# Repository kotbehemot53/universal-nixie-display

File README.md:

Universal Nixie Display
=======================

This is the central project for the open source software and hardware for the Universal Nixie Display.
The display is something more than a desktop nixie clock - it can be whatever you want it to be by
displaying not only time but also weather data or any data you want it to display.

**At the moment it is a work in progress.**

Physical Components
-------------------

The display is modular. Each board works on its own (or with a different master), the default
configuration is:

- **Nixie board** (top): up to 6 nixie tubes (attached via pluggable socket boards with current-limiting
  trimmers, so various nixie models can be used) + up to 2 neon lamps. Driven by an ATmega328P that
  receives commands over I²C (address `0x4`).
- **VFD board** (bottom): one IV-18 8-digit 7-segment VFD tube. Driven by an ATmega328P that receives
  commands over I²C (address `0x5`).
- **Pi hat**: sits on a Raspberry Pi, sends commands to the boards above, takes power from an external
  supply and distributes it, and exposes connectors for control buttons / knobs and the power button.
- **Socket boards**: small per-tube-model boards (IN-14, Z573M) and a neon lamp board that plug into
  the nixie board.

Operating principles
--------------------

The microcontrollers provide low-level control over the displays - multiplexing, dimming, displaying
letters or digits, simple animations. The Raspberry communicates with them using I²C and sends simple
commands (what characters to display, at what brightness etc.). There are python scripts on the
Raspberry that can obtain various data (e.g. weather data from Ruuvi sensors, time from an RTC,
whatever else the user wants) and pass it to be displayed on the nixies and VFD using provided python
libraries that wrap the microcontroller commands in an easy-to-use API.

By default the nixies are meant to be used as the "main" display, whereas the VFD is a "secondary"
display, used to show currently chosen options etc. But it's up to the user to decide how they want to
use them.

Repository layout
-----------------

```
firmware/
  nixie-controller/   PlatformIO project, ATmega328P firmware for the nixie board
  vfd-controller/     PlatformIO project, ATmega328P firmware for the VFD board
software/
  raspberry/          Python scripts + systemd units for the Raspberry Pi master
hardware/
  nixie-board/        KiCad project of the nixie board
  vfd-board/          KiCad project of the VFD board
  pi-hat/             KiCad project of the Raspberry Pi hat
  sockets/            KiCad projects of the tube socket boards (in14, z573m, neon)
  lib/                Shared KiCad symbol / footprint / 3D libraries used by the boards above
scratch/
  kicad-experiments/  Throwaway KiCad experiments, not part of the product
```

See `hardware/README.md` for the board naming history, PCB variants and fabrication files.

Each firmware directory is a self-contained PlatformIO project - open it directly in PlatformIO / your
IDE. Everything in this repository is licensed under the GPLv3 (see `LICENSE`).

History
-------

This repository was assembled from several previous ones (the firmware and Raspberry code used to live
in separate repos pulled in as git submodules, the hardware lived in an older private repo). Their git
histories were rewritten into subdirectories and merged here, so `git log --follow` works on the
imported files. Old feature branches were kept under the `nixie-controller/`, `vfd-controller/` and
`raspberry/` branch prefixes, VFD firmware releases are tagged `vfd-controller/<version>`.

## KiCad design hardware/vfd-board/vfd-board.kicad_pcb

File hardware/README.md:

Hardware
========

KiCad projects for all boards of the Universal Nixie Display. Files are KiCad 6/7 format
(`kicad_sch` version 20211123 / 20230121, `kicad_pcb` version 20211014 / 20221018), open them with
KiCad 7 or newer and let it upgrade the format when you first save.

```
nixie-board/    top board: up to 6 nixies + 2 neons, ATmega328P, I2C slave 0x4
vfd-board/      bottom board: IV-18 VFD, ATmega328P, I2C slave 0x5
pi-hat/         Raspberry Pi hat: power in, I2C master, buttons / knobs, power button
sockets/
  in14/         IN-14 nixie socket board (plugs into nixie-board)
  z573m/        Z573M nixie socket board (plugs into nixie-board)
  neon/         neon lamp board (plugs into nixie-board)
lib/            shared symbol / footprint / 3D model libraries (see lib/README.md)
```

Every board directory has the same shape:

- `<board>.kicad_pro / .kicad_sch / .kicad_pcb` - the current design,
- `<board>-bom.csv` - BOM exported from the schematic (where one existed),
- `sym-lib-table` / `fp-lib-table` - project library tables, all pointing into `../lib` (or `../../lib`
  for the socket boards) via `${KIPRJMOD}`,
- `fab/` - gerber zips that were actually sent to a fab house, kept as-is for reference,
- `variants/` - alternative PCB layouts of the same schematic (autorouter pre-fills, different track
  styles, earlier revisions). They are standalone `.kicad_pro` + `.kicad_pcb` pairs, open them directly.
  They are kept for reference only, the file next to the `.kicad_sch` is the current one,
- `images/` - schematic exports and 3D renders.

Symbols and footprints are embedded in the schematic / PCB files, so the boards open and render even if
a library entry is missing. The library tables only matter when you want to update a part from its
library.

Checking library resolution
---------------------------

Library links were verified headless with KiCad 10.0.1 (`kicad-cli pcb drc` / `sch erc` with
`--severity-all`, then filter for `lib_footprint_issues` / `lib_symbol_issues`). All project libraries
resolve. The remaining "not found in library" reports come from parts that the *official* KiCad
libraries renamed or removed since the boards were drawn, not from this repository:

| Reference in the design                              | Boards                 | Status in KiCad 10 official libs                          |
|------------------------------------------------------|------------------------|-----------------------------------------------------------|
| `Button_Switch_THT:SW_TH_Tactile_Omron_B3F-10xx`     | nixie-board, vfd-board | split into `SW_TH_Tactile_Omron_B3F-100x` / `-102x` / ... |
| `Symbol:Symbol_HighVoltage_Type2_CopperTop_VerySmall`| nixie-board, vfd-board | removed, only `Symbol_HighVoltage_Triangle_*` remain      |
| `Connector:Conn_01x02_Male` / `_Female` / `Conn_01x03_Male` / `Conn_01x07_Female` | nixie-board, vfd-board, sockets | moved to `Connector_Generic`     |
| `Device:Q_NMOS_SGD`, `Device:Q_NPN_CBE`             | pi-hat-tht variant     | replaced by `Q_NMOS_GSD` / `Q_NPN_BCE` pin-order variants |

The `variants/` directories carry their own `fp-lib-table` / `sym-lib-table` (same entries, one `../`
deeper), because KiCad treats whatever directory the `.kicad_pro` sits in as the project root.

The embedded copies still work, so nothing needs to change unless a part is re-placed from the library.
"Does not match its copy in the library" warnings are expected for the same reason (embedded 2022/2023
copies vs. current library versions). `kibuzzard-*` footprints are text labels generated by the
KiBuzzard plugin and never had a library.

3D models
---------

Standard-library 3D models are referenced as `${KICAD6_3DMODEL_DIR}/<lib>.3dshapes/<name>.step`. KiCad 7+
maps the old versioned variable to the current install automatically. The references were originally
`.wrl`; KiCad 9+ ships only `.step` files and does *not* fall back from `.wrl` to `.step`, so every
generic part rendered as missing until the extensions were rewritten. Five models were dropped or renamed
upstream and still show as missing in the 3D viewer, which is cosmetic:

| Model                                                             | Board                   |
|-------------------------------------------------------------------|-------------------------|
| `Potentiometer_THT/Potentiometer_Bourns_3386F_Vertical` (9x)      | nixie-board             |
| `Button_Switch_THT/SW_TH_Tactile_Omron_B3F-10xx`                  | vfd-board               |
| `Module/Raspberry_Pi_Zero_Socketed_THT_FaceDown_MountingHoles`    | vfd-board, pi-hat       |
| `Connector_USB/USB_Micro-B_Amphenol_10103594-0001LF_Horizontal`   | pi-hat                  |
| `Connector_Wire/SolderWire-0.75sqmm_1x02_P4.8mm_D1.25mm_OD2.3mm`  | pi-hat                  |

Vendored SamacSys models live in `lib/SamacSys_Parts.3dshapes/` and are referenced via `${KIPRJMOD}`.

Naming history
--------------

The boards were renamed when the projects were moved into this repository. Old names still appear in
title blocks, net names and library nicknames (`Nixiecock1`, `nixieCockB`), which were intentionally
left alone so nothing inside the design files had to be touched apart from 3D model paths.

| Old project (piclock repo)       | Here                    | Notes                                              |
|----------------------------------|-------------------------|----------------------------------------------------|
| `kicad/nixiecock1`               | `nixie-board`           | "Board A"                                          |
| `kicad/nixiecockB`               | `vfd-board`             | "Board B"                                          |
| `kicad/pihat/pihat` `pihat_smd.kicad_sch/.kicad_pro` | `pi-hat`  | SMD version, current schematic                     |
| `kicad/pihat/pihat` `pihat_smd-rounded-blah.kicad_pcb` | `pi-hat.kicad_pcb` | current layout (rounded tracks), the one that was fabbed |
| `kicad/pihat/pihat` `pihat_smd.kicad_pcb` | `pi-hat/variants/pi-hat_unrounded` | same layout before track rounding      |
| `kicad/pihat/pihat` `pihat.*`    | `pi-hat/variants/pi-hat-tht` | older THT version, has its own schematic      |
| `kicad/IN-14Board`               | `sockets/in14`          | file names unchanged (`in14board.*`)               |
| `kicad/z573mBoard`               | `sockets/z573m`         | file names unchanged (`z573mBoard.*`)              |
| `kicad/neonBoard`                | `sockets/neon`          | file names unchanged (`neonBoard.*`)               |
| `kicad/xprmnt`                   | `../scratch/kicad-experiments` | was gitignored before                       |

Fabrication files vs. layouts (from file timestamps, verify before reusing):

- `pi-hat/fab/gerber5.zip` matches `pi-hat.kicad_pcb` (the rounded-track layout).
- `nixie-board/fab/gerber_A2`, `gerber_A3` and `vfd-board/fab/gerber_B1..B3` predate the last PCB
  edits of those boards; treat the highest number as the last one ordered.
- `sockets/in14/fab/gerbers7.zip` and `sockets/z573m/fab/gerber3.zip` match the current PCBs.

What was dropped on import
--------------------------

Regenerable or per-user files were not carried over: `*-backups/`, `.history/`, `fp-info-cache`,
`*.kicad_prl`, `*.kicad_sch-bak`, `*.xml` netlists, lock files, unzipped gerber directories that also
existed as zips, and the vendor library zips (`KiCadLibs-master.zip`, SamacSys `LIB_*.zip`) whose
relevant content is now in `lib/`.

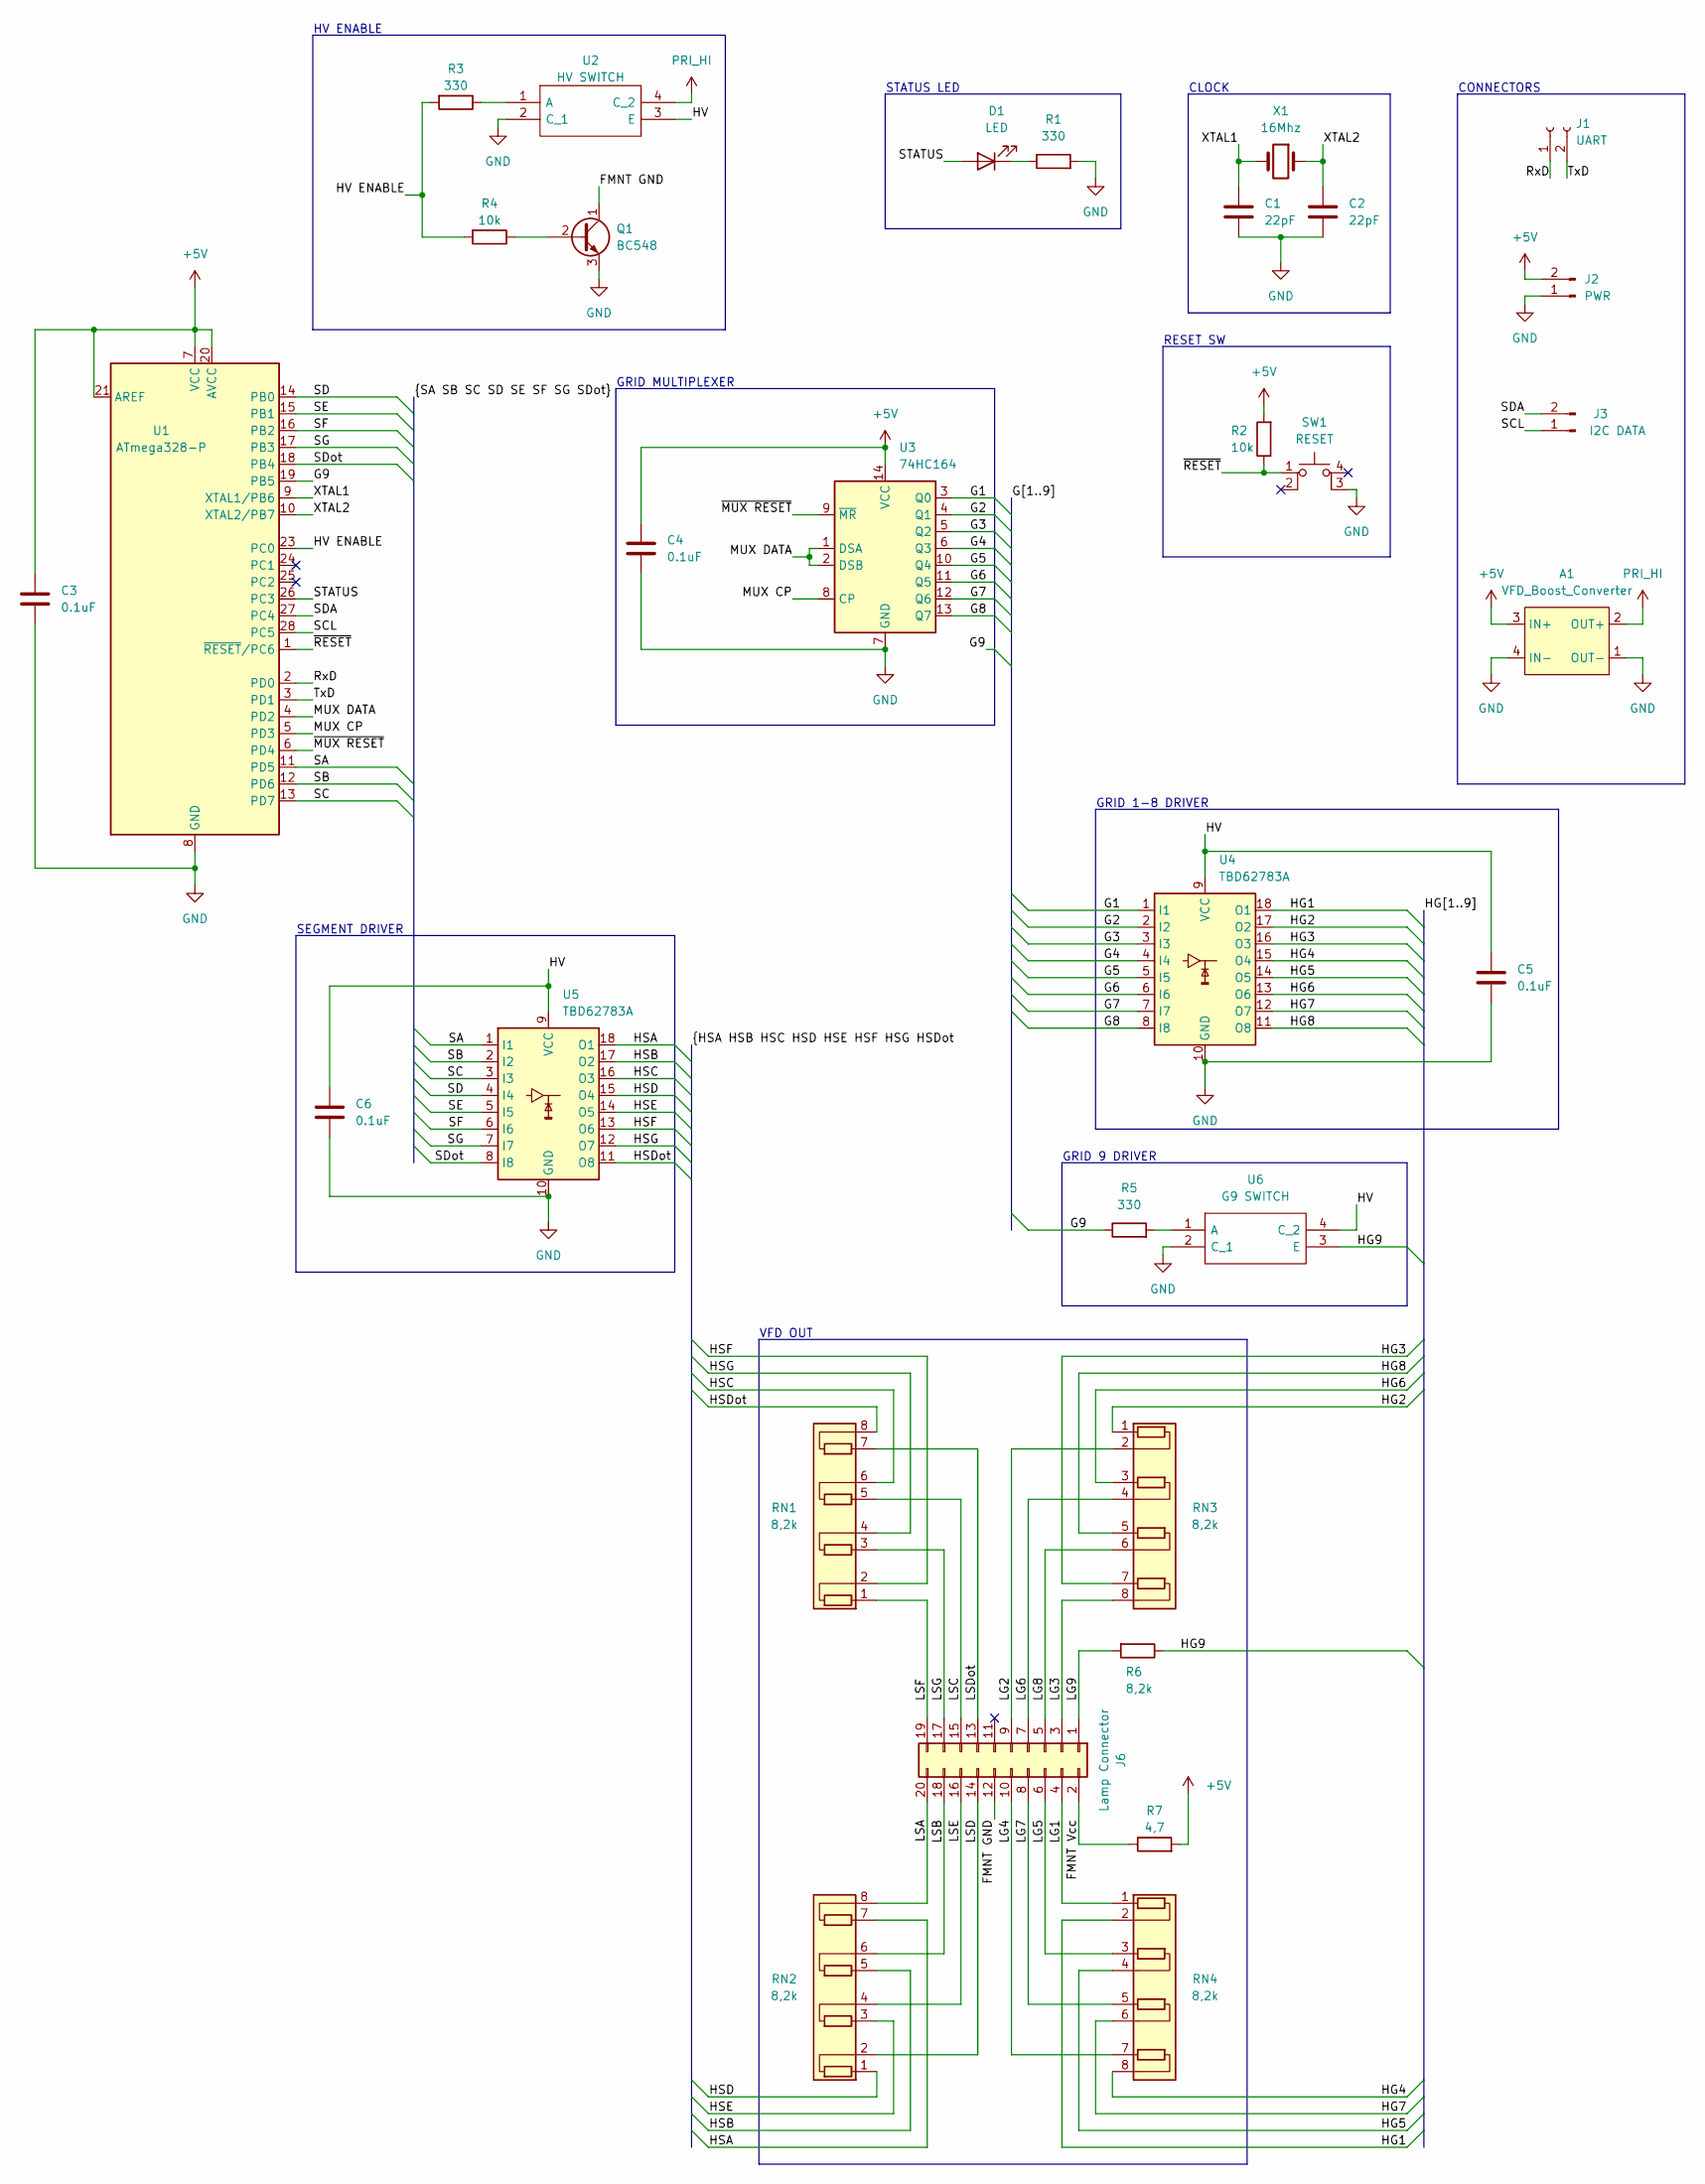
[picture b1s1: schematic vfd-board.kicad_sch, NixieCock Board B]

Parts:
A1: VFD_Boost_Converter; VFD Boost Converter
C1, C2: 22pF; C_Disc_D3.0mm_W1.6mm_P2.50mm
C3, C4, C5, C6: 0.1uF; C_Disc_D5.0mm_W2.5mm_P2.50mm
D1: LED; LED_D3.0mm
J1: UART; PinHeader_1x02_P2.54mm_Vertical
J2: PWR; JST_XH_B2B-XH-A_1x02_P2.50mm_Vertical
J3: I2C DATA; JST_XH_B2B-XH-A_1x02_P2.50mm_Vertical
J6: Lamp Connector; IDC-Header_2x10_P2.54mm_Vertical
Q1: BC548; TO-92_Inline
R1, R3, R5: 330; R_Axial_DIN0207_L6.3mm_D2.5mm_P10.16mm_Horizontal
R2, R4: 10k; R_Axial_DIN0207_L6.3mm_D2.5mm_P10.16mm_Horizontal
R6: 8,2k; R_Axial_DIN0207_L6.3mm_D2.5mm_P10.16mm_Horizontal
R7: 4,7; R_Axial_DIN0207_L6.3mm_D2.5mm_P10.16mm_Horizontal
RN1, RN2, RN3, RN4: 8,2k; R_Array_SIP8
SW1: RESET; SW_TH_Tactile_Omron_B3F-10xx
U1: ATmega328-P; DIP-28_W7.62mm_Socket
U2: HV SWITCH; DIP762W56P254L469H470Q4N; Mouser Part Number 782-SFH619A
U3: 74HC164; DIP-14_W7.62mm_Socket
U4, U5: TBD62783A; DIP-18_W7.62mm_Socket
U6: G9 SWITCH; DIP762W56P254L469H470Q4N; Mouser Part Number 782-SFH619A
X1: 16Mhz; Crystal_HC49-4H_Vertical

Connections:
+5V: A1.3 (IN+), C3.1, C4.1, J2.2, R2.2, R7.2, U1.7 (VCC), U1.20 (AVCC), U1.21 (AREF), U3.14 (VCC)
/FMNT GND: J6.12, Q1.1 (C)
/FMNT Vcc: J6.2, R7.1
/G1: U3.3 (Q0), U4.1 (I1)
/G2: U3.4 (Q1), U4.2 (I2)
/G3: U3.5 (Q2), U4.3 (I3)
/G4: U3.6 (Q3), U4.4 (I4)
/G5: U3.10 (Q4), U4.5 (I5)
/G6: U3.11 (Q5), U4.6 (I6)
/G7: U3.12 (Q6), U4.7 (I7)
/G8: U3.13 (Q7), U4.8 (I8)
/G9: R5.1, U1.19 (PB5)
/HG1: RN4.2 (R1.2), U4.18 (O1)
/HG2: RN3.1 (R1.1), U4.17 (O2)
/HG3: RN3.7 (R4.1), U4.16 (O3)
/HG4: RN4.8 (R4.2), U4.15 (O4)
/HG5: RN4.4 (R2.2), U4.14 (O5)
/HG6: RN3.3 (R2.1), U4.13 (O6)
/HG7: RN4.6 (R3.2), U4.12 (O7)
/HG8: RN3.5 (R3.1), U4.11 (O8)
/HG9: R6.1, U6.3 (E)
/HSA: RN2.7 (R4.1), U5.18 (O1)
/HSB: RN2.5 (R3.1), U5.17 (O2)
/HSC: RN1.6 (R3.2), U5.16 (O3)
/HSD: RN2.1 (R1.1), U5.15 (O4)
/HSDot: RN1.8 (R4.2), U5.11 (O8)
/HSE: RN2.3 (R2.1), U5.14 (O5)
/HSF: RN1.2 (R1.2), U5.13 (O6)
/HSG: RN1.4 (R2.2), U5.12 (O7)
/HV: C5.1, C6.1, U2.3 (E), U4.9 (VCC), U5.9 (VCC), U6.4 (C_2)
/HV ENABLE: R3.2, R4.2, U1.23 (PC0)
/LG1: J6.4, RN4.1 (R1.1)
/LG2: J6.9, RN3.2 (R1.2)
/LG3: J6.3, RN3.8 (R4.2)
/LG4: J6.10, RN4.7 (R4.1)
/LG5: J6.6, RN4.3 (R2.1)
/LG6: J6.7, RN3.4 (R2.2)
/LG7: J6.8, RN4.5 (R3.1)
/LG8: J6.5, RN3.6 (R3.2)
/LG9: J6.1, R6.2
/LSA: J6.20, RN2.8 (R4.2)
/LSB: J6.18, RN2.6 (R3.2)
/LSC: J6.15, RN1.5 (R3.1)
/LSD: J6.14, RN2.2 (R1.2)
/LSDot: J6.13, RN1.7 (R4.1)
/LSE: J6.16, RN2.4 (R2.2)
/LSF: J6.19, RN1.1 (R1.1)
/LSG: J6.17, RN1.3 (R2.1)
/MUX CP: U1.5 (PD3), U3.8 (CP)
/MUX DATA: U1.4 (PD2), U3.1 (DSA), U3.2 (DSB)
/RxD: J1.1, U1.2 (PD0)
/SA: U1.11 (PD5), U5.1 (I1)
/SB: U1.12 (PD6), U5.2 (I2)
/SC: U1.13 (PD7), U5.3 (I3)
/SCL: J3.1, U1.28 (PC5)
/SD: U1.14 (PB0), U5.4 (I4)
/SDA: J3.2, U1.27 (PC4)
/SDot: U1.18 (PB4), U5.8 (I8)
/SE: U1.15 (PB1), U5.5 (I5)
/SF: U1.16 (PB2), U5.6 (I6)
/SG: U1.17 (PB3), U5.7 (I7)
/STATUS: D1.2 (A), U1.26 (PC3)
/TxD: J1.2, U1.3 (PD1)
/XTAL1: C1.1, U1.9 (XTAL1/PB6), X1.2
/XTAL2: C2.1, U1.10 (XTAL2/PB7), X1.1
/~MUX RESET: U1.6 (PD4), U3.9 (~MR)
/~RESET: R2.1, SW1.1, U1.1 (~RESET/PC6)
GND: A1.1 (OUT-), A1.4 (IN-), C1.2, C2.2, C3.2, C4.2, C5.2, C6.2, J2.1, Q1.3 (E), R1.2, SW1.3 (K), U1.8 (GND), U1.22 (GND), U2.2 (C_1), U3.7 (GND), U4.10 (GND), U5.10 (GND), U6.2 (C_1)
unnamed: D1.1 (K), R1.1
unnamed: Q1.2 (B), R4.1
unnamed: R3.1, U2.1 (A)
unnamed: R5.2, U6.1 (A)
PRI_HI: A1.2 (OUT+), U2.4 (C_2)

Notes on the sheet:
RESET SW
GRID 1-8 DRIVER
GRID 9 DRIVER
SEGMENT DRIVER
VFD OUT
GRID MULTIPLEXER
STATUS LED
CONNECTORS
CLOCK
HV ENABLE

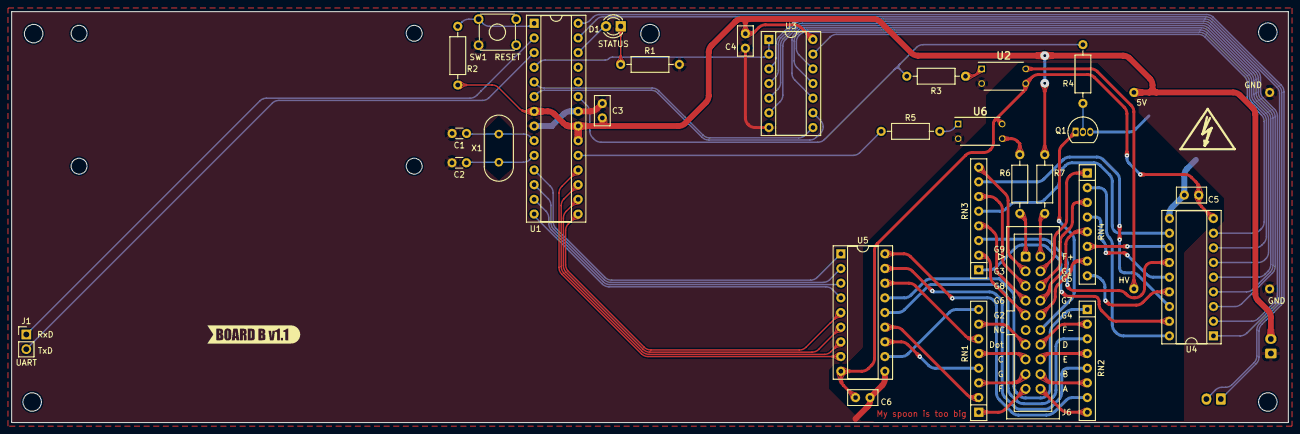
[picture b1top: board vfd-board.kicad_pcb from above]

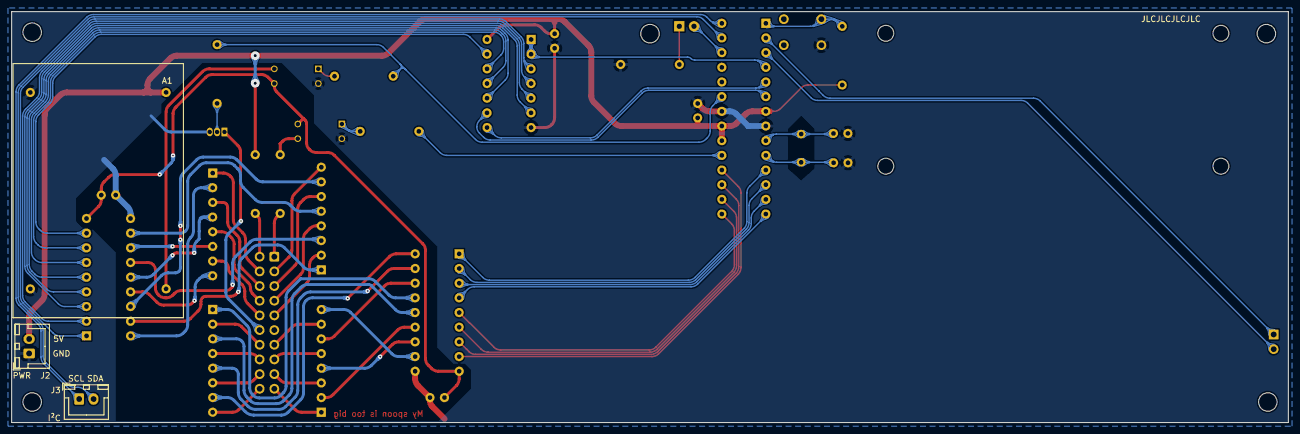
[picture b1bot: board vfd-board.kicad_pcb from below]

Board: 2 copper layers, 221.0 x 71.1 mm, 37 parts (3 on the bottom side), 73 nets.

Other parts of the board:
A2: Raspberry_Pi_Zero_Socketed_THT_FaceDown_MountingH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; Raspberry_Pi_Zero_Socketed_THT_FaceDown_MountingHoles
SYM_HV: Symbol_HighVoltage_Type2_CopperTop_VerySmall
kibuzzard-629EA45D: G***; kibuzzard-629EA45D
kibuzzard-6293E725: G***; kibuzzard-6293E725
kibuzzard-6293E830: G***; kibuzzard-6293E830

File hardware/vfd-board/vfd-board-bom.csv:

"Source:","H:\_Moje_dydy\Documents\Projekty\__sources\piclock\kicad\nixiecockB\nixiecockB.kicad_sch"
"Date:","25.06.2022 10:28:06"
"Tool:","Eeschema (6.0.0)"
"Generator:","E:\Programy\KiCad\6.0\bin\scripting\plugins/bom_csv_grouped_by_value_with_fp.py"
"Component Count:","32"
"Ref","Qnty","Value","Cmp name","Footprint","Description","Vendor"
"A1, ","1","VFD_Boost_Converter","VFD_Boost_Converter","nixieCockB:VFD Boost Converter","",""
"C1, C2, ","2","22pF","C","Capacitor_THT:C_Disc_D3.0mm_W1.6mm_P2.50mm","Unpolarized capacitor",""
"C3, C4, C5, C6, ","4","0.1uF","C","Capacitor_THT:C_Disc_D5.0mm_W2.5mm_P2.50mm","Unpolarized capacitor",""
"D1, ","1","LED","LED","LED_THT:LED_D3.0mm","Light emitting diode",""
"J1, ","1","UART","Conn_01x02_Female","Connector_PinHeader_2.54mm:PinHeader_1x02_P2.54mm_Vertical","Generic connector, single row, 01x02, script generated (kicad-library-utils/schlib/autogen/connector/)",""
"J2, ","1","PWR","Conn_01x02_Male_3","Connector_JST:JST_XH_B2B-XH-A_1x02_P2.50mm_Vertical","Generic connector, single row, 01x02, script generated (kicad-library-utils/schlib/autogen/connector/)",""
"J3, ","1","I2C DATA","Conn_01x02_Male","Connector_JST:JST_XH_B2B-XH-A_1x02_P2.50mm_Vertical","Generic connector, single row, 01x02, script generated (kicad-library-utils/schlib/autogen/connector/)",""
"J6, ","1","Lamp Connector","Conn_02x10_Odd_Even","Connector_IDC:IDC-Header_2x10_P2.54mm_Vertical","Generic connector, double row, 02x10, odd/even pin numbering scheme (row 1 odd numbers, row 2 even numbers), script generated (kicad-library-utils/schlib/autogen/connector/)",""
"Q1, ","1","BC548","BC548","Package_TO_SOT_THT:TO-92_Inline","0.1A Ic, 30V Vce, Small Signal NPN Transistor, TO-92",""
"R1, R3, R5, ","3","330","R","Resistor_THT:R_Axial_DIN0207_L6.3mm_D2.5mm_P10.16mm_Horizontal","Resistor",""
"R2, R4, ","2","10k","R","Resistor_THT:R_Axial_DIN0207_L6.3mm_D2.5mm_P10.16mm_Horizontal","Resistor",""
"R6, ","1","8,2k","R","Resistor_THT:R_Axial_DIN0207_L6.3mm_D2.5mm_P10.16mm_Horizontal","Resistor",""
"R7, ","1","4,7","R","Resistor_THT:R_Axial_DIN0207_L6.3mm_D2.5mm_P10.16mm_Horizontal","Resistor",""
"RN1, RN2, RN3, RN4, ","4","8,2k","R_Pack04_SIP","Resistor_THT:R_Array_SIP8","4 resistor network, parallel topology, SIP package",""
"SW1, ","1","RESET","SW_MEC_5E","Button_Switch_THT:SW_TH_Tactile_Omron_B3F-10xx","MEC 5E single pole normally-open tactile switch",""
"U1, ","1","ATmega328-P","ATmega328-P","Package_DIP:DIP-28_W7.62mm_Socket","20MHz, 32kB Flash, 2kB SRAM, 1kB EEPROM, DIP-28",""
"U2, ","1","HV SWITCH","SFH619A","SamacSys_Parts:DIP762W56P254L469H470Q4N","Vishay SFH619A DC Input Photodarlington Output Optocoupler, Through Hole, 4-Pin DIP",""
"U3, ","1","74HC164","74HC164","Package_DIP:DIP-14_W7.62mm_Socket","8-bit serial-in parallel-out shift register",""
"U4, U5, ","2","TBD62783A","TBD62783A","Package_DIP:DIP-18_W7.62mm_Socket","8-Channel Source Type Transistor Array, TTL and CMOS compatible, 500mA, 50V, DIP-18/SOP-18/SSOP-18/SOIC-18W",""
"U6, ","1","G9 SWITCH","SFH619A","SamacSys_Parts:DIP762W56P254L469H470Q4N","Vishay SFH619A DC Input Photodarlington Output Optocoupler, Through Hole, 4-Pin DIP",""
"X1, ","1","16Mhz","Crystal","Crystal:Crystal_HC49-4H_Vertical","Two pin crystal",""

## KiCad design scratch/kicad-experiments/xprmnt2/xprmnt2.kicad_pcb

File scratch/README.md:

Scratch
=======

Experiments and throwaway work that is not part of the product but is worth keeping around.

- `kicad-experiments/` - old KiCad experiments (`xprmnt1`, `xprmnt2`), imported from the gitignored
  `kicad/xprmnt` directory of the previous hardware repo. `xprmnt2` references DigiKey libraries from a
  machine-local path in its library tables; the symbols and footprints are embedded so it still opens.

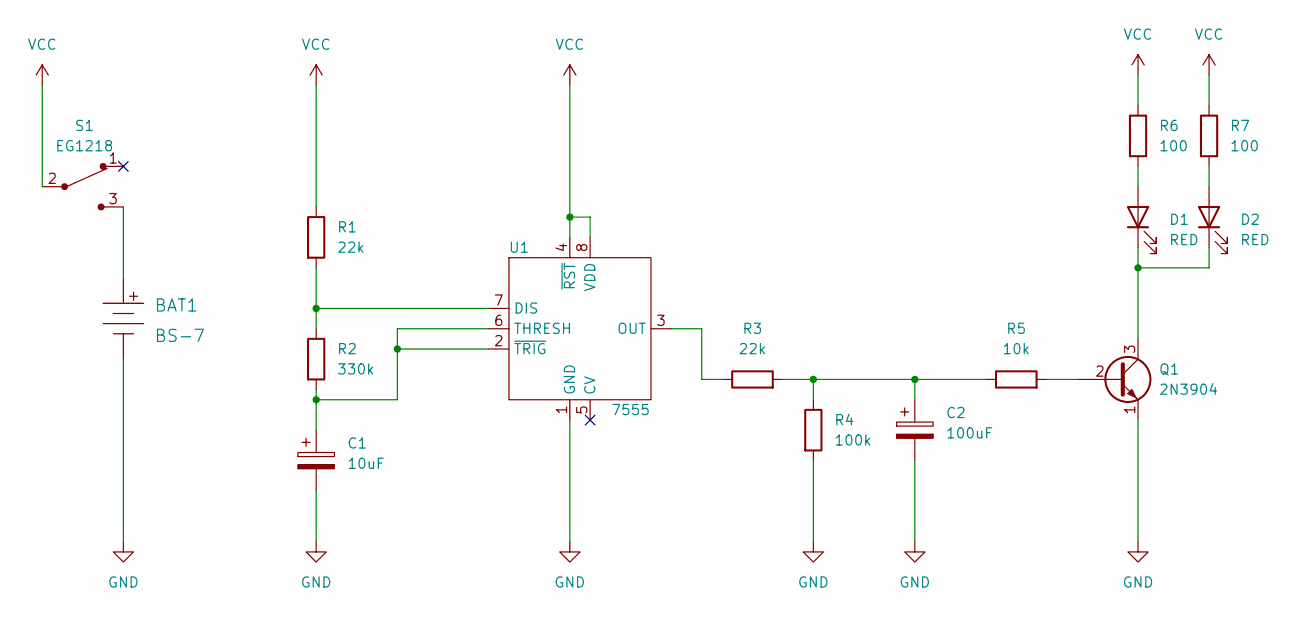
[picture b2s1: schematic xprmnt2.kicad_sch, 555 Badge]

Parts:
BAT1: BS-7; Battery_Holder_Coin_2032_BS-7; MPN BS-7; Digi-Key_PN BS-7-ND
C1: 10uF; CP_Radial_D5.0mm_P2.00mm
C2: 100uF; CP_Radial_D6.3mm_P2.50mm
D1, D2: RED; LED_D3.0mm
Q1: 2N3904; TO-92_Inline
R1, R3: 22k; R_Axial_DIN0207_L6.3mm_D2.5mm_P7.62mm_Horizontal
R2: 330k; R_Axial_DIN0207_L6.3mm_D2.5mm_P7.62mm_Horizontal
R4: 100k; R_Axial_DIN0207_L6.3mm_D2.5mm_P7.62mm_Horizontal
R5: 10k; R_Axial_DIN0207_L6.3mm_D2.5mm_P7.62mm_Horizontal
R6, R7: 100; R_Axial_DIN0207_L6.3mm_D2.5mm_P7.62mm_Horizontal
S1: EG1218; Switch_Slide_11.6x4mm_EG1218; MPN EG1218; Digi-Key_PN EG1903-ND
U1: 7555; ICM7555-PDIP

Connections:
GND: BAT1.Neg, C1.2, C2.2, Q1.1 (E), R4.2, U1.1 (GND)
unnamed: BAT1.Pos, S1.3
unnamed: C1.1, R2.2, U1.2 (~TRIG), U1.6 (THRESH)
unnamed: C2.1, R3.2, R4.1, R5.1
unnamed: D1.1 (K), D2.1 (K), Q1.3 (C)
unnamed: D1.2 (A), R6.2
unnamed: D2.2 (A), R7.2
unnamed: Q1.2 (B), R5.2
unnamed: R1.2, R2.1, U1.7 (DIS)
unnamed: R3.1, U1.3 (OUT)
VCC: R1.1, R6.1, R7.1, S1.2, U1.4 (~RST), U1.8 (VDD)

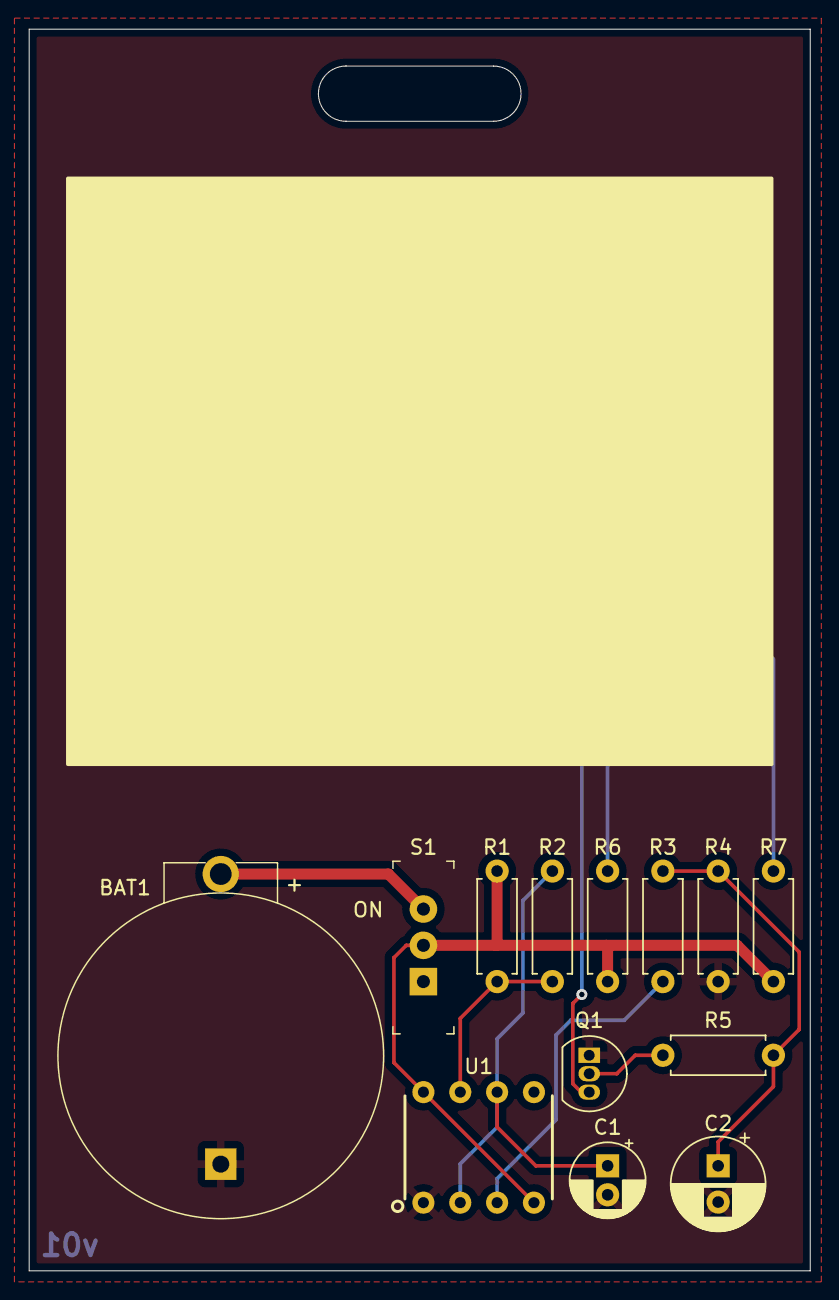
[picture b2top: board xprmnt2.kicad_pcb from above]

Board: 2 copper layers, 53.8 x 85.6 mm, 15 parts (0 on the bottom side), 11 nets.

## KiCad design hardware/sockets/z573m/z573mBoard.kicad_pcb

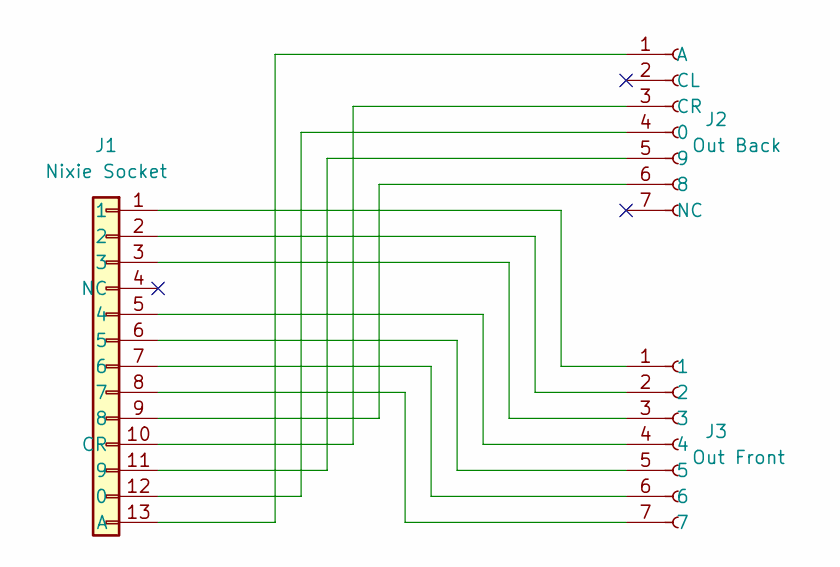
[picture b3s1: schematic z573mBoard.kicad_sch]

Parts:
J1: Nixie Socket; Z570M
J2: Out Back; PinHeader_1x07_P2.54mm_Vertical
J3: Out Front; PinHeader_1x07_P2.54mm_Vertical

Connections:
unnamed: J1.1, J3.1
unnamed: J1.2, J3.2
unnamed: J1.3, J3.3
unnamed: J1.5 (4), J3.4
unnamed: J1.6 (5), J3.5
unnamed: J1.7 (6), J3.6
unnamed: J1.8 (7), J3.7
unnamed: J1.9 (8), J2.6 (8)
unnamed: J1.10 (CR), J2.3 (CR)
unnamed: J1.11 (9), J2.5 (9)
unnamed: J1.12 (0), J2.4 (0)
unnamed: J1.13 (A), J2.1 (A)

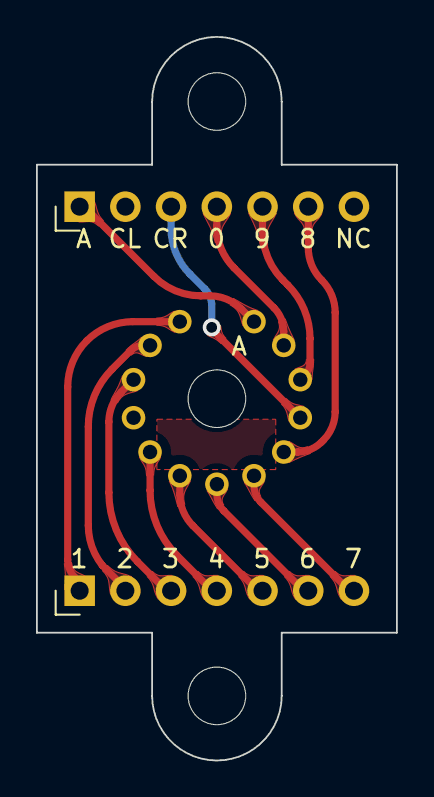
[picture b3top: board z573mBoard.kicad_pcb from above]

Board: 2 copper layers, 20.0 x 40.2 mm, 3 parts (0 on the bottom side), 12 nets.

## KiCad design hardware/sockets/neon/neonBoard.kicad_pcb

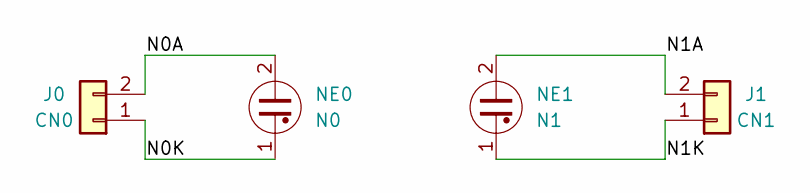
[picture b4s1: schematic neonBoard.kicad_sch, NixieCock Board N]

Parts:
J0: CN0; PinHeader_1x02_P2.54mm_Vertical
J1: CN1; PinHeader_1x02_P2.54mm_Vertical
NE0: N0; PinHeader_1x02_P2.54mm_Vertical
NE1: N1; PinHeader_1x02_P2.54mm_Vertical

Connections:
/N0A: J0.2, NE0.2
/N0K: J0.1, NE0.1
/N1A: J1.2, NE1.2
/N1K: J1.1, NE1.1

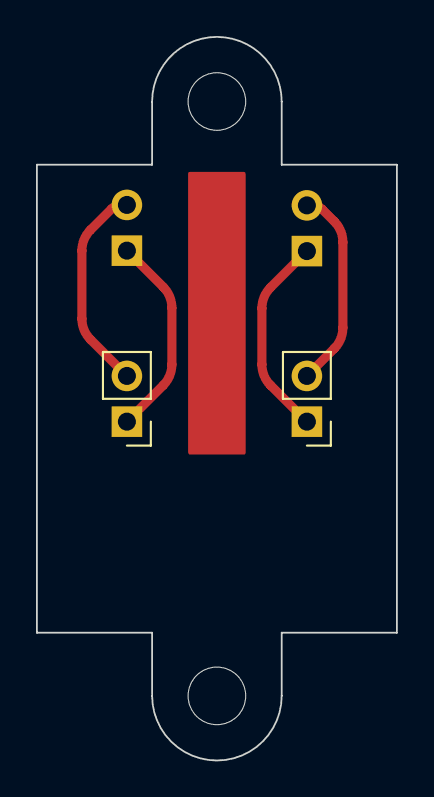
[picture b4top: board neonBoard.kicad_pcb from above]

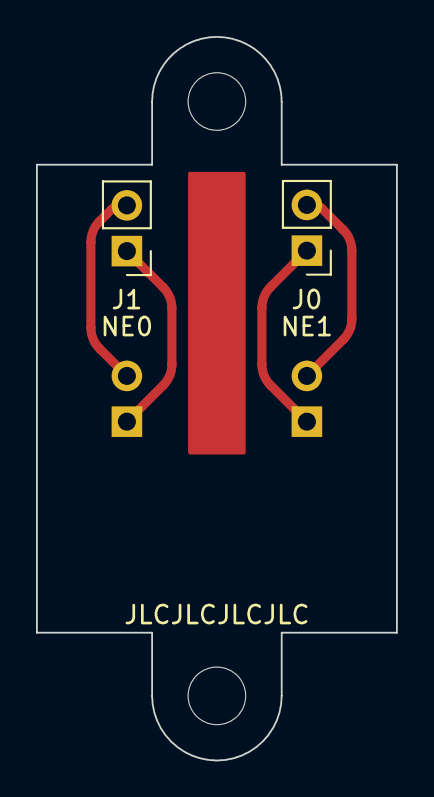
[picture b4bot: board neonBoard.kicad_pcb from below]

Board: 2 copper layers, 20.0 x 40.2 mm, 4 parts (2 on the bottom side), 4 nets.

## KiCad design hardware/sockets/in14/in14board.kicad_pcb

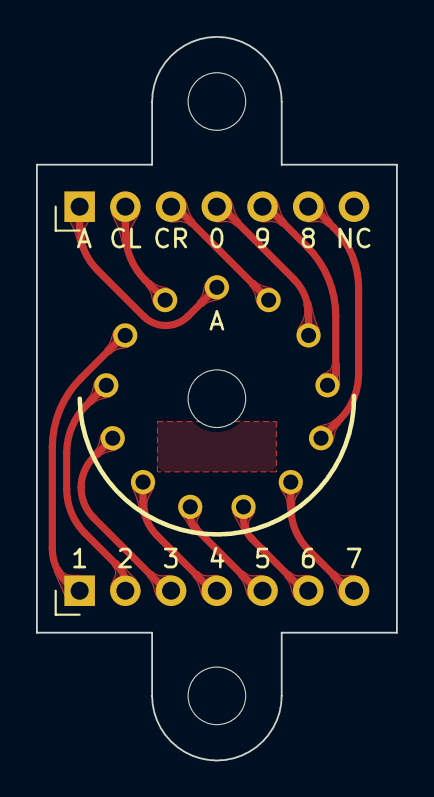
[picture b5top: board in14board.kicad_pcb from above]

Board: 2 copper layers, 20.0 x 40.2 mm, 3 parts (0 on the bottom side), 13 nets.

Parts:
J1: IN-14; nixies-us-IN-14
J2: Out Back; PinHeader_1x07_P2.54mm_Vertical
J3: Out Front; PinHeader_1x07_P2.54mm_Vertical

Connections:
unnamed: J1.0, J2.4 (0)
unnamed: J1.1, J3.1
unnamed: J1.2, J3.2
unnamed: J1.3, J3.3
unnamed: J1.4, J3.4
unnamed: J1.5, J3.5
unnamed: J1.6, J3.6
unnamed: J1.7, J3.7
unnamed: J1.8, J2.6 (8)
unnamed: J1.9, J2.5 (9)
unnamed: J1.A, J2.1 (A)
unnamed: J1.LHDP (CL), J2.2 (CL)
unnamed: J1.RHDP (CR), J2.3 (CR)

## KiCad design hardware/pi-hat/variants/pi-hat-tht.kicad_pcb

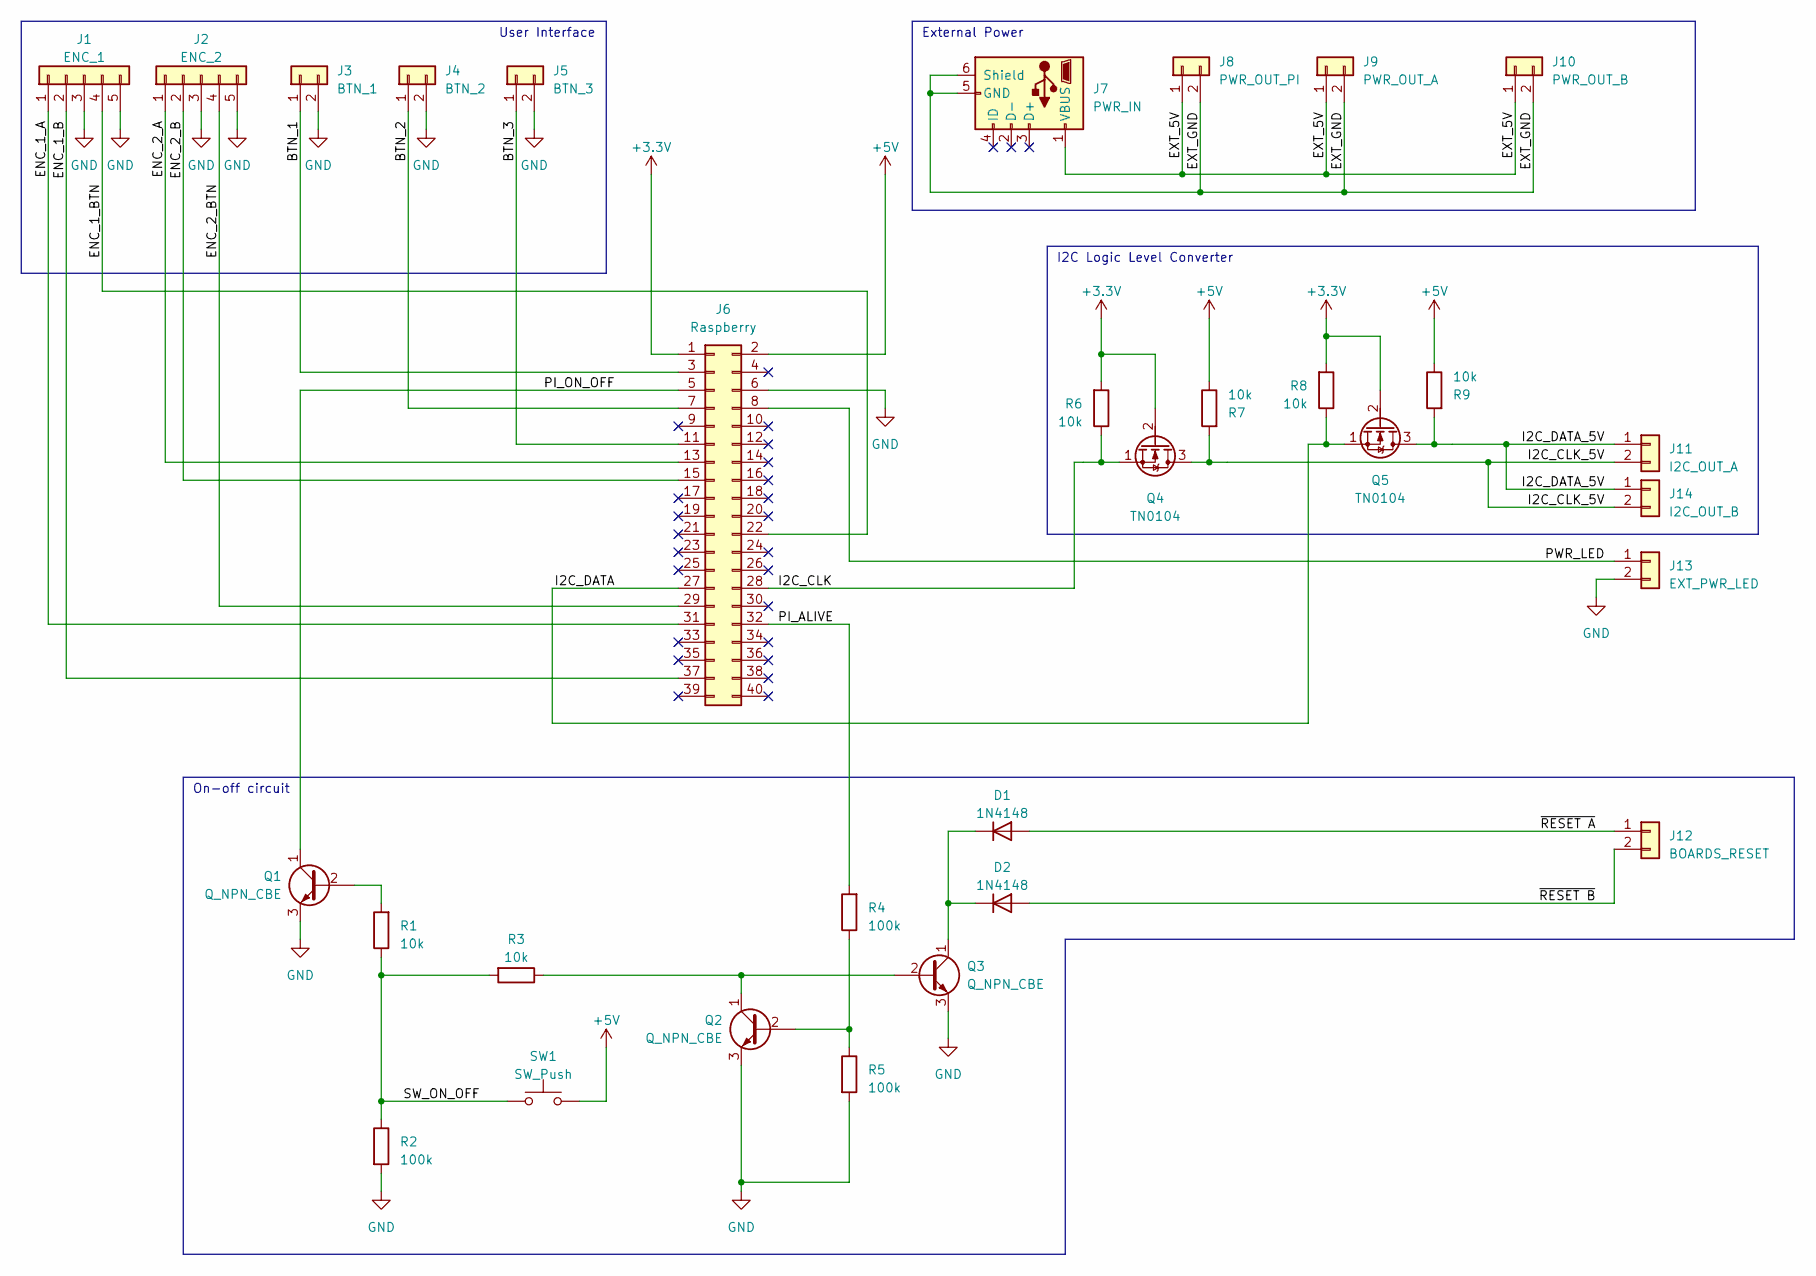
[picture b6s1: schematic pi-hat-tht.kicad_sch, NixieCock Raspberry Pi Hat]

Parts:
D1, D2: 1N4148; D_DO-34_SOD68_P7.62mm_Horizontal
J1: ENC_1; JST_XH_S5B-XH-A_1x05_P2.50mm_Horizontal
J2: ENC_2; JST_XH_S5B-XH-A_1x05_P2.50mm_Horizontal
J3: BTN_1; JST_XH_B2B-XH-A_1x02_P2.50mm_Vertical
J4: BTN_2; JST_XH_B2B-XH-A_1x02_P2.50mm_Vertical
J5: BTN_3; JST_XH_B2B-XH-A_1x02_P2.50mm_Vertical
J6: Raspberry; PinSocket_2x20_P2.54mm_Vertical
J7: PWR_IN; USB_Micro-B_Amphenol_10103594-0001LF_Horizontal
J8: PWR_OUT_PI; SolderWire-0.75sqmm_1x02_P4.8mm_D1.25mm_OD2.3mm
J9: PWR_OUT_A; JST_XH_B2B-XH-A_1x02_P2.50mm_Vertical
J10: PWR_OUT_B; JST_XH_B2B-XH-A_1x02_P2.50mm_Vertical
J11: I2C_OUT_A; JST_XH_B2B-XH-A_1x02_P2.50mm_Vertical
J12: BOARDS_RESET; JST_XH_B2B-XH-A_1x02_P2.50mm_Vertical
J13: EXT_PWR_LED; JST_XH_B2B-XH-A_1x02_P2.50mm_Vertical
J14: I2C_OUT_B; JST_XH_B2B-XH-A_1x02_P2.50mm_Vertical
Q1, Q2, Q3: Q_NPN_CBE; TO-92L_Inline
Q4, Q5: TN0104; TO-92L_Inline
R1, R3, R6, R7, R8, R9: 10k; R_Axial_DIN0207_L6.3mm_D2.5mm_P10.16mm_Horizontal
R2, R4, R5: 100k; R_Axial_DIN0207_L6.3mm_D2.5mm_P10.16mm_Horizontal
SW1: SW_Push; JST_XH_B2B-XH-A_1x02_P2.50mm_Vertical

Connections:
+3.3V: J6.1, Q4.2 (G), Q5.2 (G), R6.2, R8.2
+5V: J6.2, R7.1, R9.1, SW1.2
/BTN_1: J3.1, J6.3
/BTN_2: J4.1, J6.7
/BTN_3: J5.1, J6.11
/ENC_1_A: J1.1, J6.31
/ENC_1_B: J1.2, J6.37
/ENC_1_BTN: J1.4, J6.22
/ENC_2_A: J2.1, J6.13
/ENC_2_B: J2.2, J6.15
/ENC_2_BTN: J2.4, J6.29
/EXT_5V: J7.1 (VBUS), J8.1, J9.1, J10.1
/EXT_GND: J7.5 (GND), J7.6 (Shield), J8.2, J9.2, J10.2
/I2C_CLK: J6.28, Q4.1 (S), R6.1
/I2C_CLK_5V: J11.2, J14.2, Q4.3 (D), R7.2
/I2C_DATA: J6.27, Q5.1 (S), R8.1
/I2C_DATA_5V: J11.1, J14.1, Q5.3 (D), R9.2
/PI_ALIVE: J6.32, R4.2
/PI_ON_OFF: J6.5, Q1.1 (C)
/PWR_LED: J6.8, J13.1
/SW_ON_OFF: R1.1, R2.1, R3.2, SW1.1
/~RESET A: D1.2 (A), J12.1
/~RESET B: D2.2 (A), J12.2
GND: J1.3, J1.5, J2.3, J2.5, J3.2, J4.2, J5.2, J6.6, J13.2, Q1.3 (E), Q2.3 (E), Q3.3 (E), R2.2, R5.2
unnamed: D1.1 (K), D2.1 (K), Q3.1 (C)
unnamed: Q1.2 (B), R1.2
unnamed: Q2.2 (B), R4.1, R5.1
unnamed: Q2.1 (C), Q3.2 (B), R3.1

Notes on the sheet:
External Power
User Interface
On-off circuit
I2C Logic Level Converter

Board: 2 copper layers, 32 parts (1 on the bottom side), 28 nets, no tracks yet.

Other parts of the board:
A2: Raspberry_Pi_Zero_Socketed_THT_FaceDown_MountingH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; Raspberry_Pi_Zero_Socketed_THT_FaceDown_MountingHoles

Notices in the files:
scratch/kicad-experiments/xprmnt2/xprmnt2.kicad_pcb:
creativecommons.org/licenses/by/4.0
License: CC BY 4.0
